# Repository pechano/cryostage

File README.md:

# cryostage

Contained within the /Cryostage repository is all the resources needed to use the Arduino controlled cryostage by Johannes Lørup Buch.

This includes:
	The Arduino sketch
	
	EAGLE files for schematic and PCB (ressources)
	
	Schematics of any lasercut objects used in the project
	
	The scientific poster used to present the project

The project was a part of my PhD thesis and anything contained here has been used purely for academic purposes. 
The original research article can be found at: http://www.sciencedirect.com/science/article/pii/S0011224016300372

###########
Arduino libraries used:
###########

	MAX31855.h //Library by Rob Tillaart. Used for communicating with the MAX31855 chip. https://github.com/RobTillaart/Arduino/tree/master/libraries/MAX31855
  	PID_v1.h //The Arduino PID algorithm by Brett Beauregaard, used to control temperature in setpoint mode. https://github.com/br3ttb/Arduino-PID-Library
  	rgb_lcd.h //Grove LCD RGB Backlight library. https://github.com/Seeed-Studio/Grove_LCD_RGB_Backlight    
	math.h //Math functions used in thermistor calculations.
	Wire.h //I2C library used for communicating with the LCD.

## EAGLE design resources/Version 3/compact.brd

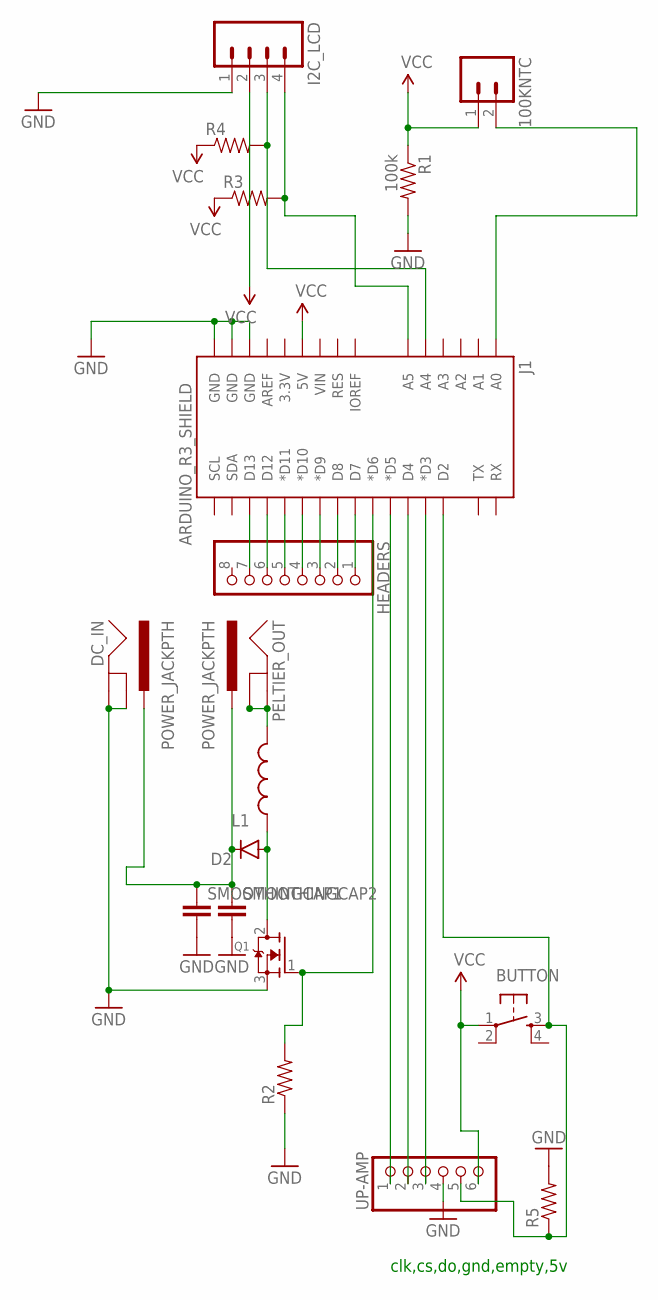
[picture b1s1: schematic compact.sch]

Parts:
100KNTC: M02LOCK; 1X02_LOCK
BUTTON: TAC_SWITCHPTH; TACTILE-PTH
D2: DIODEPTH; DIODE-1N4001
DC_IN: POWER_JACKPTH; POWER_JACK_PTH
HEADERS: PINHD-1X8BIG; 1X08-BIG
I2C_LCD: M04JST; 1X04-1.5MM_JST
J1: ARDUINO_R3_SHIELD; UNO_R3_SHIELD
L1: INDUCTORRLB0912; RLB0912
PELTIER_OUT: POWER_JACKPTH; POWER_JACK_PTH
Q1: MOSFET-NGDS_TO220V; TO220V
R1: 100k; AXIAL-0.4
R2, R3, R4, R5: RESISTORPTH-1/4W; AXIAL-0.4
SMOOTHINGCAP1, SMOOTHINGCAP2: CAPPTH3; CAP-PTH-LARGE
UP-AMP: PINHD-1X6; 1X06

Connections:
GND: DC_IN.GND, DC_IN.GNDBREAK, I2C_LCD.1, J1.GND@0 (GND), J1.GND@1 (GND), J1.GND@2 (GND), Q1.3 (S), R1.P$2 (2), R2.P$1 (1), R5.P$2 (2), SMOOTHINGCAP1.2, SMOOTHINGCAP2.2, UP-AMP.4
unnamed: D2.C, DC_IN.PWR, PELTIER_OUT.PWR, SMOOTHINGCAP1.1, SMOOTHINGCAP2.1
unnamed: I2C_LCD.3, J1.A4, R4.P$2 (2)
unnamed: J1.D6 (*D6), Q1.1 (G), R2.P$2 (2)
unnamed: J1.D5 (*D5), UP-AMP.1
unnamed: J1.D4, UP-AMP.2
unnamed: J1.D3 (*D3), UP-AMP.3
unnamed: D2.A, L1.1, Q1.2 (D)
unnamed: I2C_LCD.4, J1.A5, R3.P$2 (2)
unnamed: BUTTON.3, J1.D2, R5.P$1 (1), UP-AMP.5
unnamed: 100KNTC.2, J1.A0
unnamed: HEADERS.1, J1.D7
unnamed: HEADERS.2, J1.D8
unnamed: HEADERS.3, J1.D9 (*D9)
unnamed: HEADERS.4, J1.D10 (*D10)
unnamed: HEADERS.5, J1.D11 (*D11)
unnamed: HEADERS.6, J1.D12
unnamed: HEADERS.7, J1.D13
unnamed: L1.2, PELTIER_OUT.GND, PELTIER_OUT.GNDBREAK
VCC: 100KNTC.1, BUTTON.1, I2C_LCD.2, J1.5V, R1.P$1 (1), R3.P$1 (1), R4.P$1 (1), UP-AMP.6

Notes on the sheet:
clk,cs,do,gnd,empty,5v

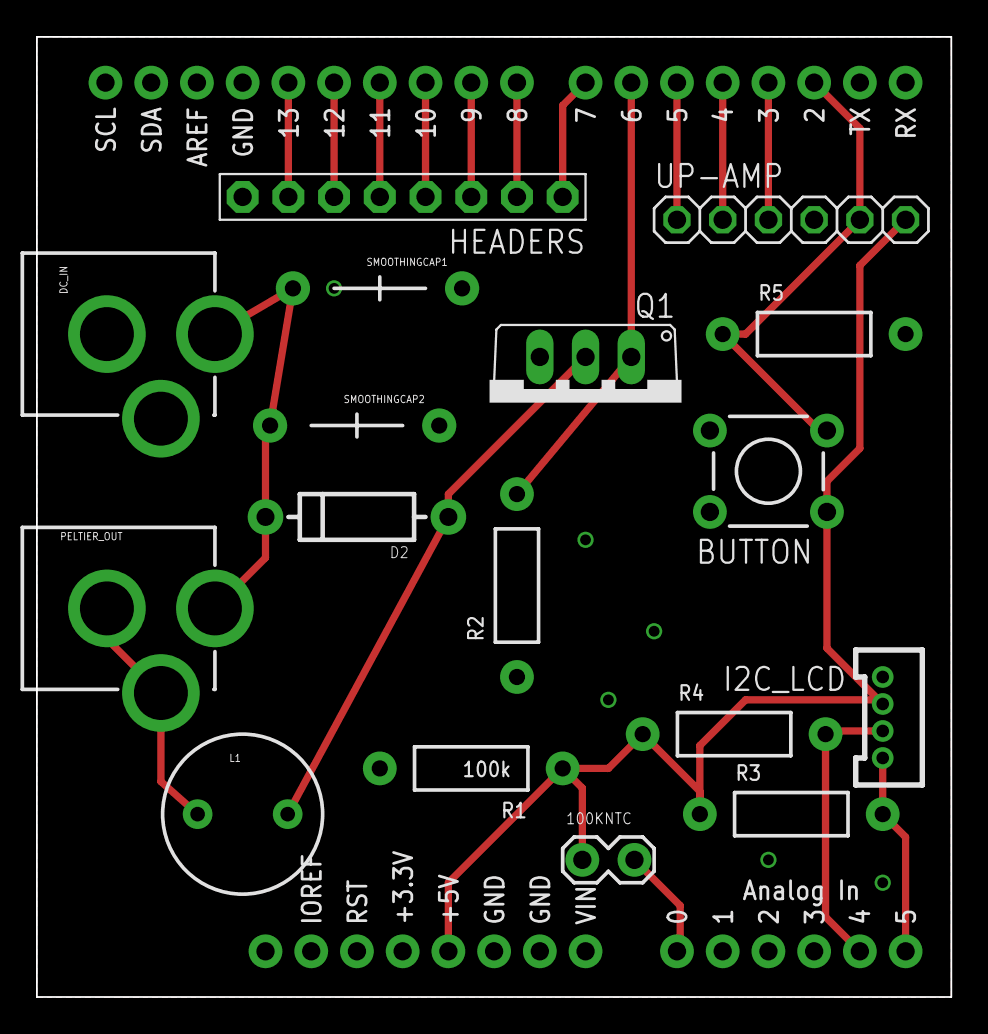
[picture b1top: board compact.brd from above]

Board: 2 copper layers, 50.8 x 53.3 mm, 18 parts (0 on the bottom side), 20 nets.

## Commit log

2015-05-06 First commit 060515
2015-05-06 Første ændring
2015-05-07 07052015 problemer med NAN
2015-05-11 code cleanu and commenting. button for potential white LED was added
2015-05-11 updated the readme to include just a bit of information
2015-05-19 Updated LCD to Grove RGB v2.0, now depends on new library
2015-05-28 28/05/15 version. Code is nearing completion. The thermistor is no longer used, but has been replaced by a pot at A0. RGB_LCD has been fully implemented and so has push buttons for the enclosure
2015-05-29 29052015. The code is nearing completion. A secondary temperature source has been implemented in the form of a 100k NTC on pin A0. The pot has been moved to A2. The Adafruit MAX31855 library will pro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
2015-06-01 first update from windows. Adafruit_max31855 has been replaced by MAX31855 by Rob Tillaart.
2015-06-01 added the version 3 PCB from EAGLE
2015-06-01 added the schematic for version 3 from EAGLE
2015-06-01 version 3 cooling block design from SketchUp
2015-06-01 Poster that was used to present version 2 and 3 of the Cryostage at Roskilde University 22/05 2015.
2015-06-15 Version used to perform the paper experiments. Very dirty code
2015-09-09 ignore list
2015-09-09 fiji macro
    contents can be added to startupmacros
2015-10-07 Added license
    GPLv3 license text added to comply with the PID library.
2015-11-05 Added the ffmpeg batches
    A text file containing both batches with instructions on getting them
    functional.
2016-04-06 sciencedirect link
    added link to the research article accompanying the development of the OSC.

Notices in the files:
parts and their libraries:
SparkFun-Connectors: Licensing: Creative Commons ShareAlike 4.0 International - https://creativecommons.org/licenses/by-sa/4.0
